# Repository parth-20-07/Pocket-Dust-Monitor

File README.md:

# Pocket Air Quality Index Monitor

## Why AQI Monitor is needed?
Carry Air Pocket Monitor before stepping out of your house in order to know the quality of the air you’re breathing. The pocket-sized air monitoring device is handy and easy to carry around.

It helps you understand the level of Particulate Matter 2.5 of your location. Works as both – real-time indoor and outdoor air quality monitoring sensor; the LCD display shows you PM reading indicating if the air is safe or not.

Having a desktop friendly version helps to determine the quality of air which can help you improving your life and work quality.

<br>

## Features of our AQI Monitor
- Shows the value of PM2.5 along with the safety level.
- Shows simultaneous value of PM1.0, PM2.5 and PM10.
- Plots the graph of PM2.5 on a graph in difference of 5 minutes.
- Approx. 1.5 hours Battery Backup.
- Type C charging support.

<br>

## How to assemble the project
1. Download the latest version of firmware from the /Firmware folder
2. Edit the Firmware as per the requirement with the help of guide provided in /Firmware/README.md
3. Order the components from the Bill of Materials as per the requirement.
4. Make the Hardware circuit
   1.  Solder them on General Purpose PCB Board using the design below (or)
   2.  Order the PCB by providing the PCB Developer with the gerber file available in /Hardware/PCB_Gerber.zip and solder all the component on it
5.  Upload the firmware on the the hardware

<br>

## How to use the device
1. Press the push button to turn on the device.
2. The device will start with a bootup screen with the company logo.
3. The landing page will show the value of PM 2.5 of screen.
4. Press the change screen button to switch between pages. The device works in 3 modes:
   1. Live PM 2.5 data screen.
   2. Live PM 1.0, PM 2.5, PM 10 data screen.
   3. PM 2.5 graph screen which plots the value of PM 2.5 in bar graph at an interval of 5 mins.

<center>

## Schematic Design

<br><br>

## PCB Design

Top View

Bottom View

## Rendered Images

</center>

## Tools Used

<br><br>

## Design Details
- Designed for: Ecologic Pvt. Ltd.
- Designed by: [Parth Patel](mailto:parth.pmech@gmail.com)

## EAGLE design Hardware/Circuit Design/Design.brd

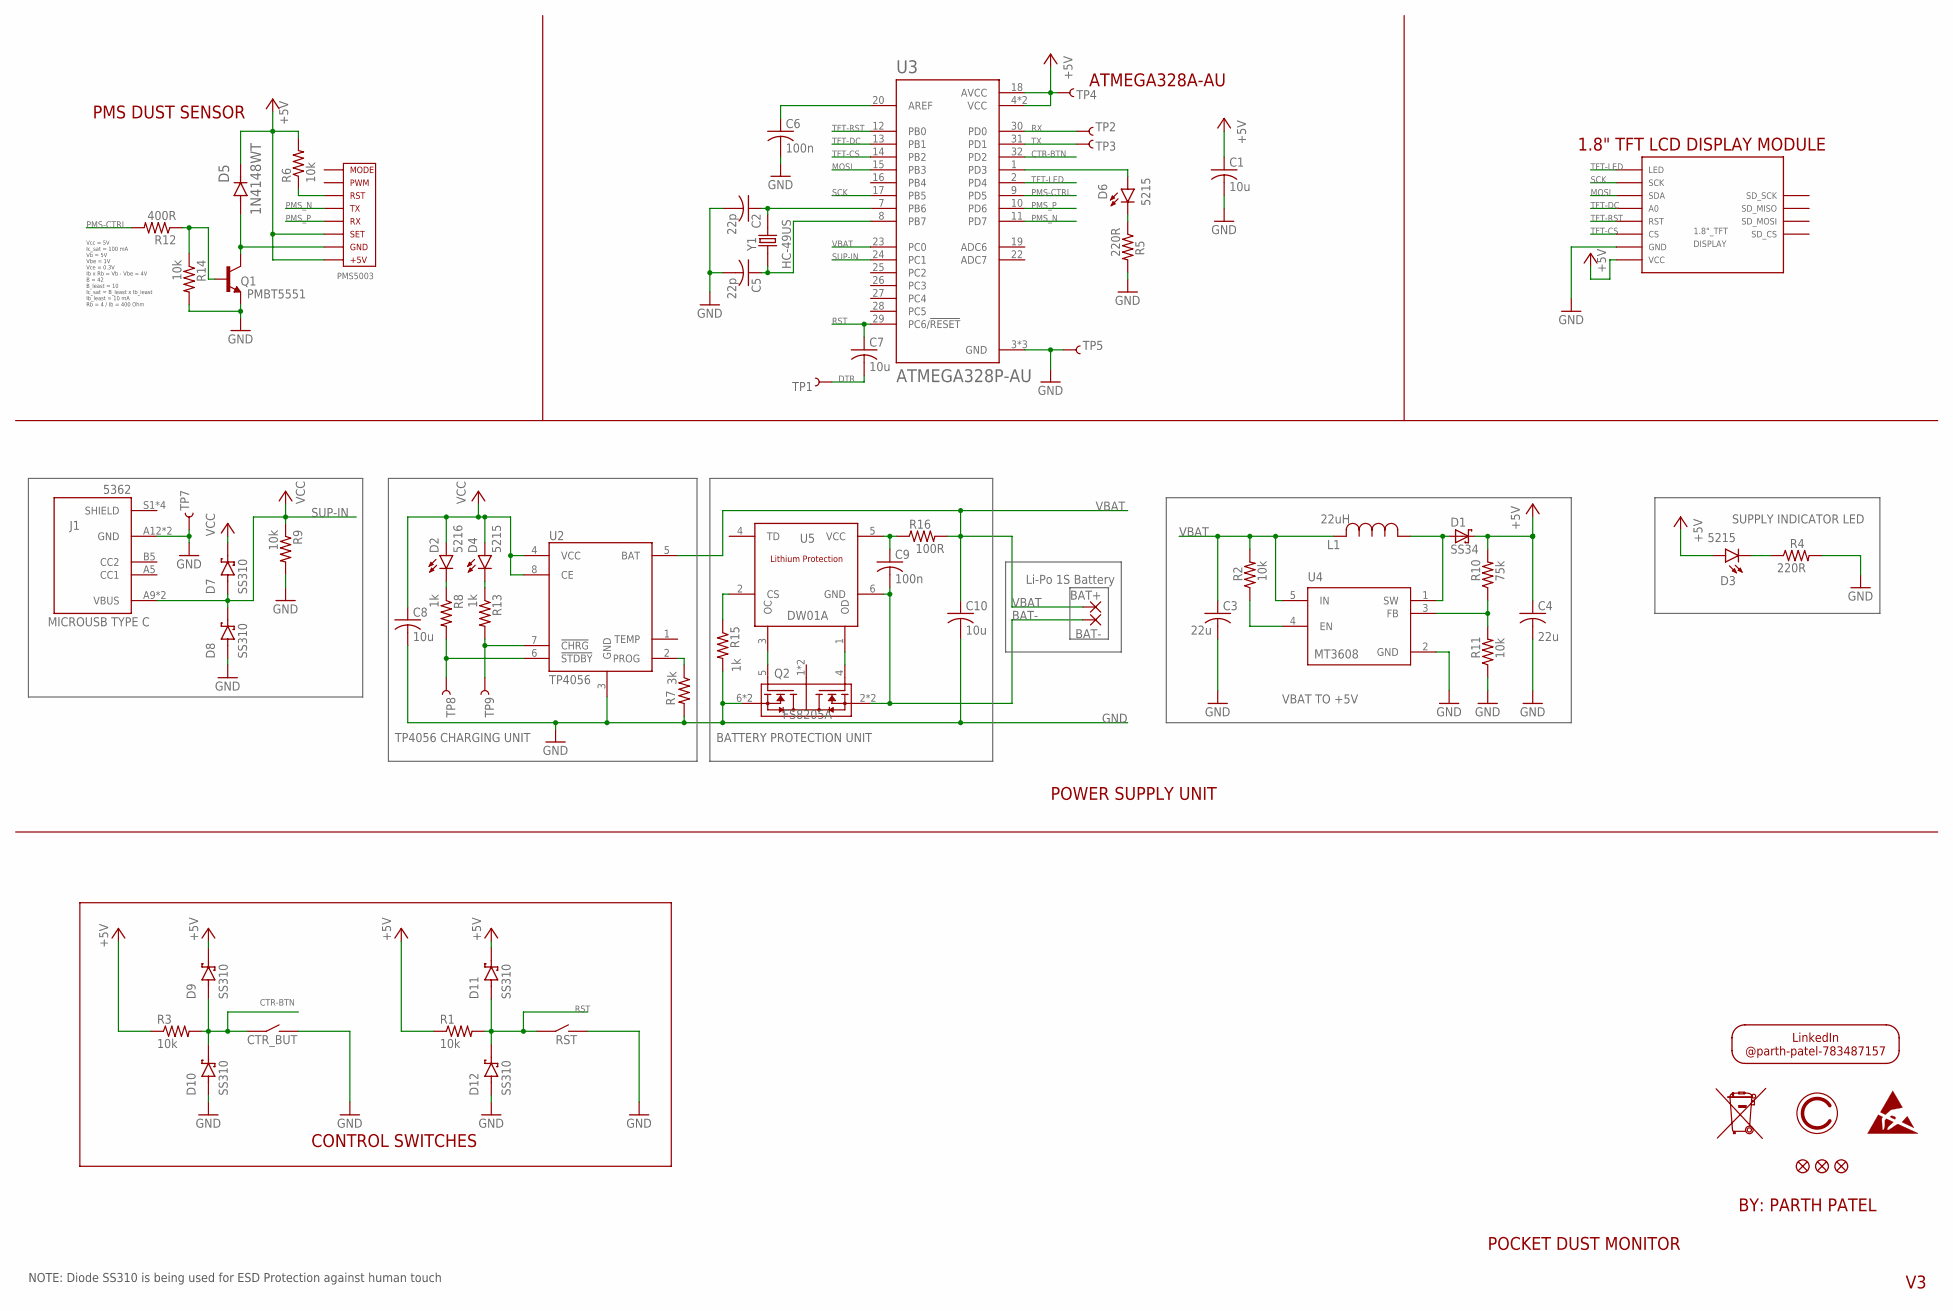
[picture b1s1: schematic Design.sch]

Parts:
BAT+: WIREPADSMD5-2,5; 5-2,5
BAT-: WIREPADSMD5-2,5; 5-2,5
C1, C7, C8, C10: 10u; C0805
C2, C5: 22p; C0805
C3, C4: 22u; C0805
C6, C9: 100n; C0805
CTR_BUT: 7058; DIP_3X6MM_SIDE_PRESS_2PIN
D1: SS34; DO214
D2: 5216; CHIP-LED0603
D3, D4, D6: 5215; CHIP-LED0603
D5: 1N4148WT; SODFL1608X70N
D7, D8, D9, D10, D11, D12: SS310; DIOM6859X262N
DISPLAY: 1.8"_TFT
FID3, FID4, FID5: FIDUCIAL""; FIDUCIAL_1MM
J1: 5362; GCT_USB4125-GF-A-0190_REVA2
L1: 22uH; INDM125125X800N
PMS5003: PMS5003
Q1: PMBT5551; SOT95P240X110-3N
Q2: FS8205A; SOP65P640X120-8N
R1, R2, R3, R6, R9, R11, R14: 10k; R0805
R4, R5: 220R; R0805
R7: 3k; R0805
R8, R13, R15: 1k; R0805
R10: 75k; R0805
R12: 400R; R0805
R16: 100R; R0805
RST: 7058; DIP_3X6MM_SIDE_PRESS_2PIN
TP1, TP2, TP3, TP4, TP5, TP7: TEST-POINT3; PAD.03X.03
TP8: ~STDBY; PAD.03X.03
TP9: ~CHRG; PAD.03X.03
U2: TP4056; SOP127P600X175-9N
U3: ATMEGA328P-AU; QFP80P900X900X120-32N
U4: MT3608; SOT95P280X145-6N
U5: DW01A; SOT23-6
U$1: LOGO_17MM; FOOTPRINT_17MM
Y1: HC-49US; XTAL_ECS-160-20-4X

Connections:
+5V: C1.1, C4.1, D1.C, D3.A, D5.D+, D9.C (K), D11.C (K), DISPLAY.VCC (+5V), PMS5003.+5V, PMS5003.SET, R1.1, R3.1, R6.2, R10.2, TP4.P$1, U3.4 (VCC), U3.6 (VCC), U3.18 (AVCC)
BAT-: BAT-.1, C9.2, Q2.2 (S1), Q2.3 (S1), U5.6 (GND)
CTR-BTN: CTR_BUT.P$1 (S1), D9.A, D10.C (K), R3.2, U3.32 (PD2)
DTR: C7.2, TP1.P$1
GND: C1.2, C2.2, C3.2, C4.2, C5.2, C6.2, C8.2, C10.2, CTR_BUT.P$2 (S2), D8.A, D10.A, D12.A, DISPLAY.GND, J1.A12 (GND), J1.B12 (GND), Q1.E, Q2.6 (S2), Q2.7 (S2), R4.2, R5.2, R7.2, R9.2, R11.1, R14.2, R15.2, RST.P$2 (S2), TP5.P$1, TP7.P$1, U2.3 (GND), U3.3 (GND), U3.5 (GND), U3.21 (GND), U4.2 (GND)
MOSI: DISPLAY.SDA, U3.15 (PB3)
unnamed: D5.D-, PMS5003.GND, Q1.C
unnamed: C5.1, U3.8 (PB7), Y1.1
unnamed: D3.C, R4.1
unnamed: Q1.B, R12.1, R14.1
unnamed: R2.1, U4.4 (EN)
unnamed: C6.1, U3.20 (AREF)
unnamed: PMS5003.RST, R6.1
unnamed: D4.C, R13.1
unnamed: D2.C, R8.1
unnamed: C2.1, U3.7 (PB6), Y1.2
unnamed: D1.A, L1.1, U4.1 (SW)
unnamed: R10.1, R11.2, U4.3 (FB)
unnamed: D6.C, R5.1
unnamed: D6.A, U3.1 (PD3)
unnamed: Q2.5 (G2), U5.3 (OC)
unnamed: R13.2, TP9.P$1, U2.7 (!CHRG)
unnamed: R8.2, TP8.P$1, U2.6 (!STDBY)
unnamed: R7.1, U2.2 (PROG)
unnamed: Q2.4 (G1), U5.1 (OD)
unnamed: R15.1, U5.2 (CS)
unnamed: C9.1, R16.1, U5.5 (VCC)
PMS-CTRL: R12.2, U3.9 (PD5)
PMS_N: PMS5003.TX, U3.11 (PD7)
PMS_P: PMS5003.RX, U3.10 (PD6)
RST: C7.1, D11.A, D12.C (K), R1.2, RST.P$1 (S1), U3.29 (PC6/!RESET)
RX: TP2.P$1, U3.30 (PD0)
SCK: DISPLAY.SCK, U3.17 (PB5)
SUP-IN: D7.A, D8.C (K), J1.A9 (VBUS), J1.B9 (VBUS), R9.1, U3.24 (PC1)
TFT-CS: DISPLAY.CS, U3.14 (PB2)
TFT-DC: DISPLAY.DC (A0), U3.13 (PB1)
TFT-LED: DISPLAY.LED, U3.2 (PD4)
TFT-RST: DISPLAY.RST, U3.12 (PB0)
TX: TP3.P$1, U3.31 (PD1)
VBAT: BAT+.1, C3.1, C10.1, L1.2, R2.2, R16.2, U2.5 (BAT), U3.23 (PC0), U4.5 (IN)
VCC: C8.1, D2.A, D4.A, D7.C (K), U2.4 (VCC), U2.8 (CE)

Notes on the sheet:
POWER SUPPLY UNIT
POCKET DUST MONITOR
BY: PARTH PATEL
CONTROL SWITCHES
PMS DUST SENSOR
PMS5003
ATMEGA328A-AU
1.8" TFT LCD DISPLAY MODULE
MICROUSB TYPE C
VBAT TO +5V
TP4056 CHARGING UNIT
Vcc = 5V Ic_sat = 100 mA Vb = 5V Vbe = 1V Vce = 0.3V Ib x Rb = Vb - Vbe = 4V B = 42 B_least = 10 Ic_sat = B_least x Ib_least Ib_least = 10 mA Rb = 4 / Ib = 400 Ohm
Li-Po 1S Battery
BATTERY PROTECTION UNIT
SUPPLY INDICATOR LED
NOTE: Diode SS310 is being used for ESD Protection against human touch

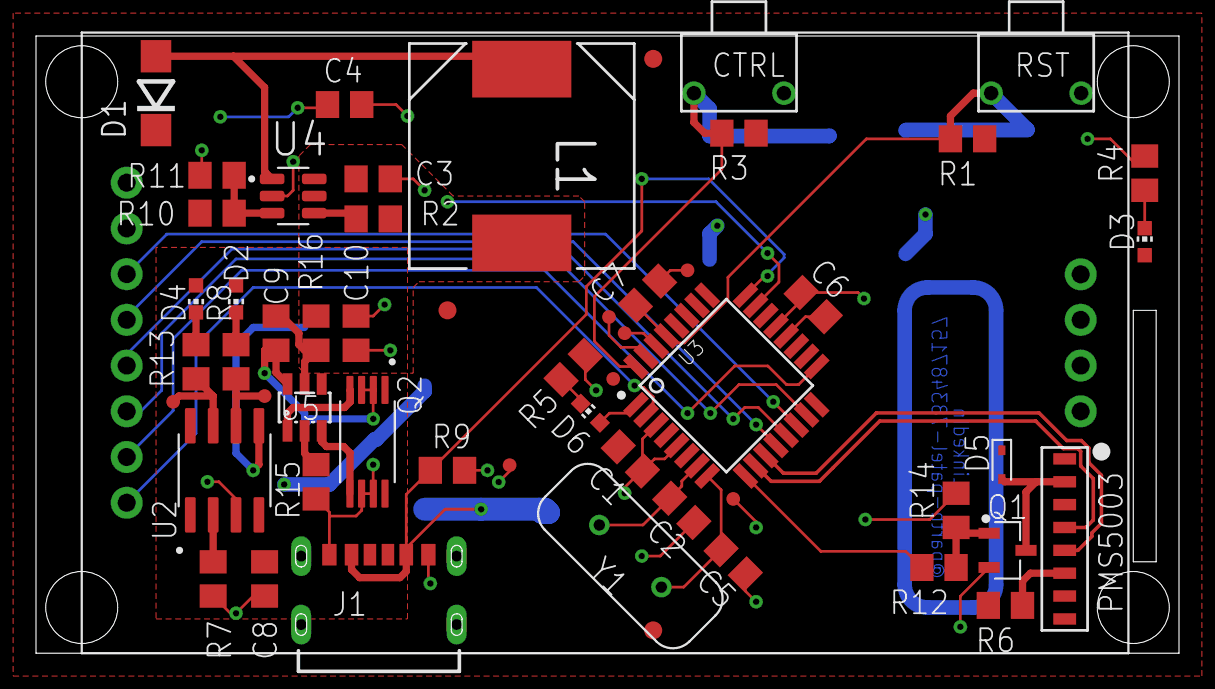
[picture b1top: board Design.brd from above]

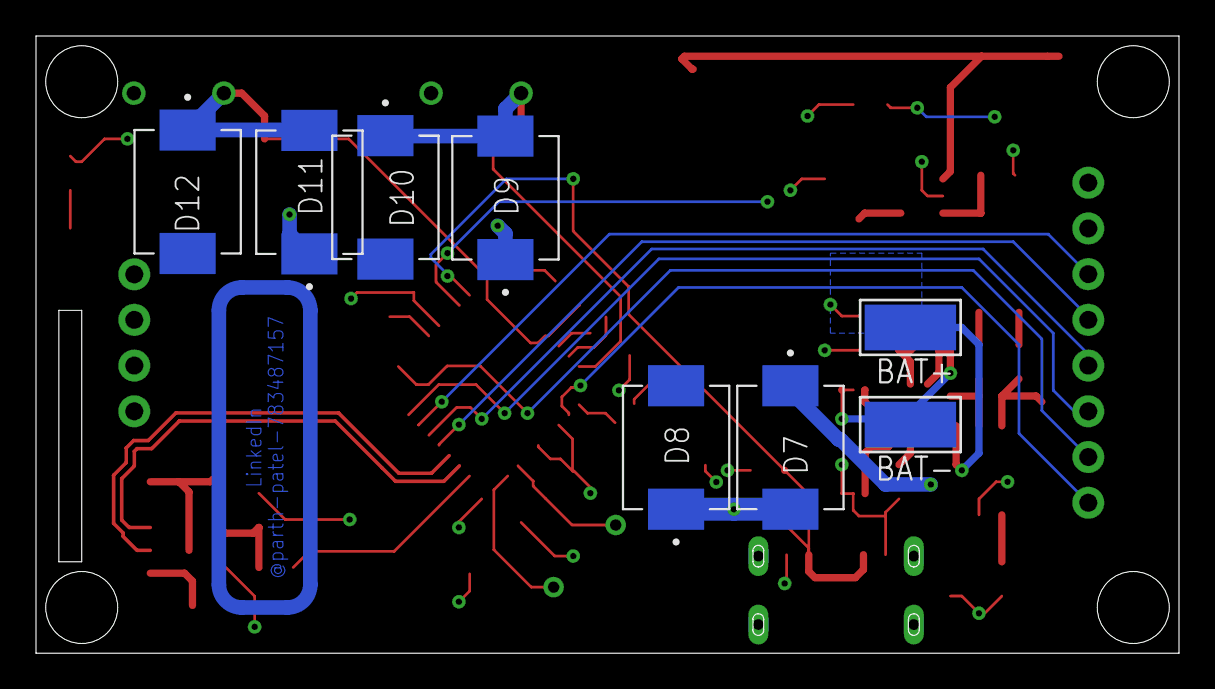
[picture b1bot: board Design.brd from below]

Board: 2 copper layers, 63.5 x 34.3 mm, 65 parts (9 on the bottom side), 41 nets.

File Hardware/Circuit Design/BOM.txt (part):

Partlist exported from D:/Backup Files/Files/Items/Internship/7. Ecologic/Ecologic Projects/Pocket Dust Monitor/Hardware/Circuit Design/Design.sch at 23-04-2022 01:57 PM

Qty Value           Device                    Package                     Parts                                    Description                                                                                                       AVAILABILITY BOM     DESCRIPTION                                                                                          MF                           MP                          PACKAGE                        POPULARITY PRICE PURCHASE-URL                                                   SPICEPREFIX                                                       
1   1.8"_TFT        1.8"_TFT                  1.8"_TFT                    DISPLAY                                                                                                                                                                                                                                                                                                                                                                                                                                                                                                                        
1   100R            R-US_R0805                R0805                       R16                                      RESISTOR, American symbol                                                                                                                                                                                                                                                                                                           85                                                                              R                                                                 
2   100n            C-USC0805                 C0805                       C6, C9                                   CAPACITOR, American symbol                                                                                                                                                                                                                                                                                                          63                                                                              C                                                                 
7   10k             R-US_R0805                R0805                       R1, R2, R3, R6, R9, R11, R14             RESISTOR, American symbol                                                                                                                                                                                                                                                                                                           85                                                                              R                                                                 
4   10u             C-USC0805                 C0805                       C1, C7, C8, C10                          CAPACITOR, American symbol                                                                                                                                                                                                                                                                                                          63                                                                              C                                                                 
1   1N4148WT        1N4148WT                  SODFL1608X70N               D5                                       Diode Switching 100V 0.125A 2-Pin SOD-523 Check availability                                                                                                                                                                                                                                                                                                                                                                                                                          
3   1k              R-US_R0805                R0805                       R8, R13, R15                             RESISTOR, American symbol                                                                                                                                                                                                                                                                                                           85                                                                              R                                                                 
2   220R            R-US_R0805                R0805                       R4, R5                                   RESISTOR, American symbol                                                                                                                                                                                                                                                                                                           85                                                                              R                                                                 
2   22p             C-USC0805                 C0805                       C2, C5                                   CAPACITOR, American symbol                                                                                                                                                                                                                                                                                                          63                                                                              C                                                                 
2   22u             C-USC0805                 C0805                       C3, C4                                   CAPACITOR, American symbol                                                                                                                                                                                                                                                                                                          63                                                                              C                                                                 
1   22uH            DR127-221-R               INDM125125X800N             L1                                       POWER INDUCTOR Check availability                                                                                 In Stock              Inductor Power Shielded Drum Core 221.5uH/220uH 20% 100KHz Ferrite 1.29A 376mOhm DCR T/R            Eaton                        DR127-221-R                 Nonstandard Eaton                         None  https://pricing.snapeda.com/search/part/DR127-221-R/?ref=eda                                                                     
1   3k              R-US_R0805                R0805                       R7                                       RESISTOR, American symbol                                                                                                                                                                                                                                                                                                           85                                                                              R                                                                 
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
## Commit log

2022-12-24 Add Project to GitHub

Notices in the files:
parts and their libraries:
SparkFun-Connectors: Licensing: Creative Commons ShareAlike 4.0 International - https://creativecommons.org/licenses/by-sa/4.0
